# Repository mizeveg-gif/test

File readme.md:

# SNMP Command Builder Library

Библиотека для построения команд конфигурации SNMP v2c и SNMP v3 для отправки через Redis stream.

## Установка

Просто скопируйте файл `snmp_command_builder.py` в ваш проект.

```bash
pip install # не требуется, библиотека использует только стандартные модули Python
```

## Быстрый старт

### SNMP v2c конфигурация

```python
from snmp_command_builder import build_snmp_v2_command
import json

# Простое создание команды для SNMP v2c
command = build_snmp_v2_command(
    community_ro="public",
    community_rw="private",
    id_device=1
)

print(json.dumps(command, indent=2))
```

### SNMP v3 конфигурация

```python
from snmp_command_builder import build_snmp_v3_command, SecurityLevel, AuthProtocol, PrivProtocol
import json

# SNMP v3 с authPriv (аутентификация + шифрование)
command = build_snmp_v3_command(
    security_name="admin_user",
    security_level=SecurityLevel.AUTH_PRIV,
    id_device=2,
    auth_protocol=AuthProtocol.SHA_256,
    auth_password="auth_secret",
    priv_protocol=PrivProtocol.AES_256,
    priv_password="priv_secret",
    context_name="network_context"
)

print(json.dumps(command, indent=2))
```

## Продвинутое использование

### Использование builder'а напрямую

```python
from snmp_command_builder import SNMPCommandBuilder

builder = SNMPCommandBuilder.from_v2_config(
    community_ro="public",
    community_rw="private",
    id_device=1
)

# Получить как dict
command = builder.build()

# Получить как JSON строку
json_string = builder.to_json(indent=2)

# Получить формат для Redis stream
stream_name, message = builder.to_redis_stream_format()
```

### Отправка в Redis stream

```python
import redis
from snmp_command_builder import SNMPCommandBuilder

# Подключение к Redis
r = redis.Redis(host='localhost', port=6379)

# Создание команды
builder = SNMPCommandBuilder.from_v3_config(
    security_name="admin",
    security_level=SecurityLevel.AUTH_PRIV,
    auth_protocol=AuthProtocol.SHA,
    auth_password="password123",
    priv_protocol=PrivProtocol.AES,
    priv_password="password456"
)

# Отправка в Redis stream
stream_name, message = builder.to_redis_stream_format()
r.xadd(stream_name, message)
```

### Кастомные группы, представления и доступ

```python
from snmp_command_builder import (
    SNMPCommandBuilder,
    SNMPGroup,
    SNMPView,
    SNMPAccess,
    AccessRights,
    ViewType,
    SecurityLevel
)

custom_groups = [
    SNMPGroup(
        group_name="my_admin_group",
        access_rights=AccessRights.READ_WRITE,
        views=["my_view"],
        notify_access=True
    )
]

custom_views = [
    SNMPView(
        view_name="my_view",
        subtree="1.3.6.1.2.1",
        mask="ff",
        type=ViewType.INCLUDED
    )
]

custom_access = [
    SNMPAccess(
        group="my_admin_group",
        context="default",
        security_level=SecurityLevel.AUTH_PRIV,
        read_view="my_view",
        write_view="my_view",
        notify_view="my_view"
    )
]

builder = SNMPCommandBuilder.from_v2_config(
    community_ro="public",
    community_rw="private",
    id_device=1,
    snmp_groups=custom_groups,
    snmp_views=custom_views,
    snmp_access=custom_access
)

command = builder.build()
```

## API Reference

### Enumerations

#### `SNMPVersion`
- `V2C` - SNMP v2c
- `V3` - SNMP v3

#### `SecurityLevel` (SNMP v3)
- `NO_AUTH_NO_PRIV` - noAuthNoPriv
- `AUTH_NO_PRIV` - authNoPriv
- `AUTH_PRIV` - authPriv

#### `AuthProtocol` (SNMP v3)
- `MD5`, `SHA`, `SHA_224`, `SHA_256`, `SHA_384`, `SHA_512`

#### `PrivProtocol` (SNMP v3)
- `DES`, `AES`, `AES_128`, `AES_192`, `AES_256`

#### `AccessRights`
- `READ_ONLY`, `READ_WRITE`

#### `ViewType`
- `INCLUDED`, `EXCLUDED`

### Data Classes

#### `SNMPGroup`
- `group_name`: str
- `access_rights`: AccessRights
- `views`: List[str]
- `security_model`: SecurityModel (default: USM)
- `notify_access`: bool (default: True)

#### `SNMPView`
- `view_name`: str
- `subtree`: str
- `mask`: str (default: "ff")
- `type`: ViewType (default: INCLUDED)

#### `SNMPAccess`
- `group`: str
- `context`: str
- `security_level`: SecurityLevel
- `read_view`: str
- `write_view`: str
- `notify_view`: str

### Основные классы и функции

#### `SNMPCommandBuilder`

Главный класс для построения команд.

**Методы класса:**
- `from_v2_config(community_ro, community_rw, id_device=0, ...)` - создать для SNMP v2c
- `from_v3_config(security_name, security_level, id_device=0, ...)` - создать для SNMP v3

**Методы экземпляра:**
- `build()` - вернуть команду как dict
- `to_json(indent=2)` - вернуть команду как JSON строку
- `to_redis_stream_format()` - вернуть tuple (stream_name, message) для Redis

#### `build_snmp_v2_command(community_ro, community_rw, id_device=0)`
Быстрая функция для создания SNMP v2c команды.

#### `build_snmp_v3_command(security_name, security_level, id_device=0, ...)`
Быстрая функция для создания SNMP v3 команды.

## Формат выходных данных

Библиотека генерирует команду следующего формата:

```json
{
  "ID_DEVICE": 0,
  "TYPE_COMMANDS": "CONFIG_GENERAL_SNMP_UPDATE",
  "DATA": {
    "snmp_version": "v2c/v3",
    "community_ro": "read-only community",
    "community_rw": "read-write community",
    "v3_security_name": "security name",
    "v3_security_level": "noAuthNoPriv/authNoPriv/authPriv",
    "v3_auth_protocol": "MD5/SHA/...",
    "v3_auth_password": "auth password",
    "v3_priv_protocol": "DES/AES/...",
    "v3_priv_password": "priv password",
    "v3_context_name": "context name",
    "snmp_groups": [...],
    "snmp_views": [...],
    "snmp_access": [...]
  },
  "TIME": "2026-04-16T08:36:12.187470Z"
}
```

## Тестирование

Запустите тесты:

```bash
python test_snmp_builder.py
```

## Лицензия

MIT

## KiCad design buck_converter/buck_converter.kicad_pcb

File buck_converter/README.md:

# Buck DC-DC Converter (LM2596S-5.0)

## Описание проекта

Проект понижающего (step-down) DC-DC преобразователя на базе микросхемы **LM2596S-5.0** для KiCad 10.

### Характеристики:
- **Входное напряжение:** 4.5V - 40V (рекомендуется 12V)
- **Выходное напряжение:** 5V (фиксированное)
- **Максимальный выходной ток:** 3A (рекомендуется до 2A)
- **Частота переключения:** 150 kHz
- **КПД:** до 88%

## Состав проекта

### Файлы:
- `buck_converter.kicad_sch` - электрическая схема
- `buck_converter.kicad_pcb` - печатная плата
- `README.md` - документация

## Компоненты

| Обозначение | Наименование | Номинал | Корпус |
|-------------|--------------|---------|--------|
| U1 | LM2596S-5.0 | Buck Regulator | TO-263-5 |
| C1 | Конденсатор | 10uF/50V | 0805 |
| C2 | Конденсатор | 22uF/16V | 1206 |
| L1 | Дроссель | 10uH/3A | 1210 |
| D1 | Диод Шоттки | SS34 (3A/40V) | SMA |
| R1 | Резистор | 1kΩ | 0805 |
| J1 | Клемма | Вход | Phoenix MKDSN 2.5/2 |
| J2 | Клемма | Выход | Phoenix MKDSN 2.5/2 |

## Схема подключения

```
VIN (12V) ──┬── C1 ──┬── U1 (VIN)
            │        │
           GND      U1 (SW) ──┬── L1 ──┬── VOUT (5V)
                              │        │
                             D1       C2
                              │        │
                             GND      GND
```

## Инструкция по использованию

1. Откройте KiCad 10
2. Выберите "File" → "Open Project"
3. Найдите и откройте файл `buck_converter.kicad_pro` (или создайте новый проект и импортируйте файлы)
4. Для редактирования схемы используйте **Schematic Editor**
5. Для редактирования платы используйте **PCB Editor**

## Рекомендации по трассировке

- **Силовые цепи:** Трассы VIN, SW и VOUT должны быть максимально широкими (минимум 1.5mm)
- **Земля:** Используйте сплошной полигон земли на нижнем слое
- **Терморазгрузка:** Убедитесь, что вывод GND микросхемы U1 имеет хорошую тепловую связь с полигоном земли
- **Компоненты:** Размещайте C1 как можно ближе к выводам VIN и GND микросхемы

## Меры предосторожности

⚠️ **Внимание!** При работе с напряжениями выше 24V соблюдайте меры безопасности:
- Не прикасайтесь к плате под напряжением
- Используйте соответствующие средства защиты
- Проверяйте полярность подключения перед подачей питания

## Лицензия

Этот проект распространяется под лицензией MIT.

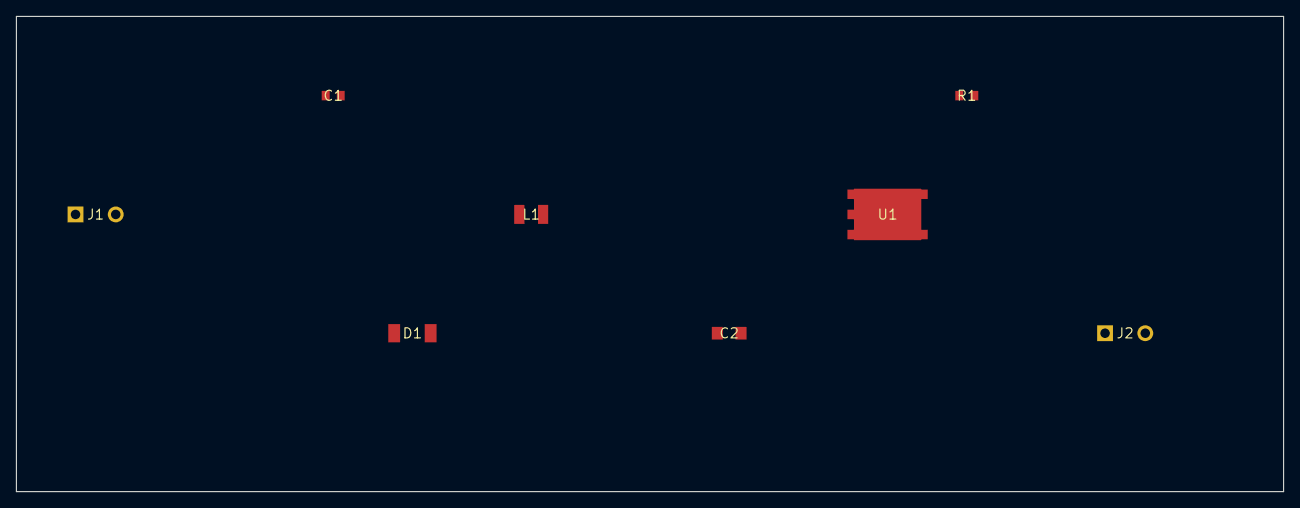
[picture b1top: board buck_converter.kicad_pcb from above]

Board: 2 copper layers, 160.0 x 60.0 mm, 8 parts (0 on the bottom side), 5 nets, no tracks yet.

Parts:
C1: 10uF; C_0805_2012Metric
C2: 22uF; C_1206_3216Metric
D1: SS34; D_SMA
J1: INPUT; TerminalBlock_Phoenix_MKDSN-2,5-2-5,08_1x02_P5.08mm_Horizon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
J2: OUTPUT; TerminalBlock_Phoenix_MKDSN-2,5-2-5,08_1x02_P5.08mm_Horizon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
L1: 10uH; L_1210_3225Metric
R1: 1k; R_0805_2012Metric
U1: LM2596S-5.0; TO-263-5

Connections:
FB: R1.1, U1.4
GND: C2.2, D1.1, J1.2, J2.2, U1.3, U1.6
SW: C1.2, D1.2, L1.1, U1.2
VIN: C1.1, J1.1, U1.1, U1.5
VOUT: C2.1, J2.1, L1.2, R1.2

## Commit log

2026-04-15 Title: Add KiCad project for LM2596S-5.0 buck converter
    Key features implemented:
    - Create .gitignore with KiCad project file exclusions
    - Add buck_converter.kicad_sch with schematic symbols for LM2596S-5.0, capacitors, inductor, diode, and terminal blocks
    - Add buck_converter.kicad_pcb with PCB layout including component footprints and copper connections
    - Add README.md with project documentation, specifications, component list, and usage instructions
    The project implements a complete step-down DC-DC converter design supporting 12V input to 5V/2A output with proper component placement and routing guidelines.
2026-04-15 update branch
2026-04-16 Title: SNMP Command Builder Library Implementation
    Key features implemented:
    - New snmp_command_builder.py file implementing complete SNMP v2c/v3 command building library with dataclasses and enums for type safety
    - Added comprehensive test suite in test_snmp_builder.py covering all SNMP versions and security levels with validation
    - Created .gitignore file to exclude Python cache files and compiled bytecode
    - Updated README.md with detailed documentation including quick start examples, API reference, and Redis integration guide
    - Implemented support for SNMP v2c community strings and SNMP v3 security models with full authentication/privacy protocols
2026-04-16 Title: Implement SNMP Command Builder and Stream Processing Service
    Key features implemented:
    - Added snmp_command_builder.py with comprehensive SNMP configuration command building capabilities supporting both v2c and v3 protocols
    - Implemented data classes for SNMP groups, views, access rules and enums for security levels, protocols, and access rights
    - Created factory methods for v2c and v3 configuration building with proper field validation and default values
    - Added Redis stream formatting functionality with to_redis_stream_format() method for direct stream publishing
    - Built convenience functions build_snmp_v2_command() and build_snmp_v3_command() for quick command generation
2026-04-16 feat: SNMP Configuration Service
    Добавлен сервис для автоматической конфигурации NET-SNMP через Redis stream:
    - snmp_config_service.py - основной сервис с поддержкой consumer groups
    - requirements.txt - зависимости Python (redis)
    - config.env.example - шаблон конфигурации
    - snmp_config_service.service - systemd unit файл
    - Dockerfile - контейнеризация сервиса
2026-04-16 **SNMP Configuration Service Implementation**
    Key features implemented:
    - New SNMPConfigService class that subscribes to Redis stream 'stream:commands' and processes SNMP configuration commands
    - SNMPConfigurator class that generates snmpd.conf files and manages NET-SNMP daemon configuration for both v2c and v3 protocols
    - Support for SNMP v2c community strings (RO/RW) and v3 security levels (noAuthNoPriv, authNoPriv, authPriv) with authentication and privacy protocols
    - Implementation of SNMP groups, views, and access control lists with proper validation and configuration generation
    - Redis consumer group management with message acknowledgment and error handling for reliable command process
2026-04-16 refactor: секционный подход к конфигурации SNMP
    - Добавлен секционный подход для управления конфигурацией snmpd.conf
    - Конфигурация разделена на маркированные секции (SNMP_V2_CONFIG, SNMP_V3_CONFIG)
    - При обновлении V2 конфигурации V3 секция автоматически удаляется и наоборот
    - Сохраняются пользовательские настройки вне секций (passpersist скрипты, sysLocation, sysContact и др.)
    - Добавлены методы: _read_current_config(), _extract_sections(),
2026-04-16 fix: pass CLI redis host/port arguments to service constructor
2026-04-16 fix: handle redis TimeoutError gracefully in command loop
2026-04-16 fix: support lowercase keys and data_command field from Redis stream
2026-04-16 fix: Correct command type extraction from Redis stream message
2026-04-16 fix: ensure V2/V3 sections are mutually exclusive and write config as string
2026-04-21 add file
